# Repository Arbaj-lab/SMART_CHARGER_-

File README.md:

A compact, efficient, and automated smart charging trigger system built using an ATtiny 402 microcontroller, relays, and an IR sensor. This project automates the charging process with a custom-designed PCB.
Features
Automated Charging Trigger: Monitors charging conditions and activates relays as required.
IR Sensor Integration: Detects specific conditions to enable/disable the charging process.
Custom PCB Design: Compact and optimized for real-world applications.
Arduino-Based Programming: Simple, modular code for easy customization.

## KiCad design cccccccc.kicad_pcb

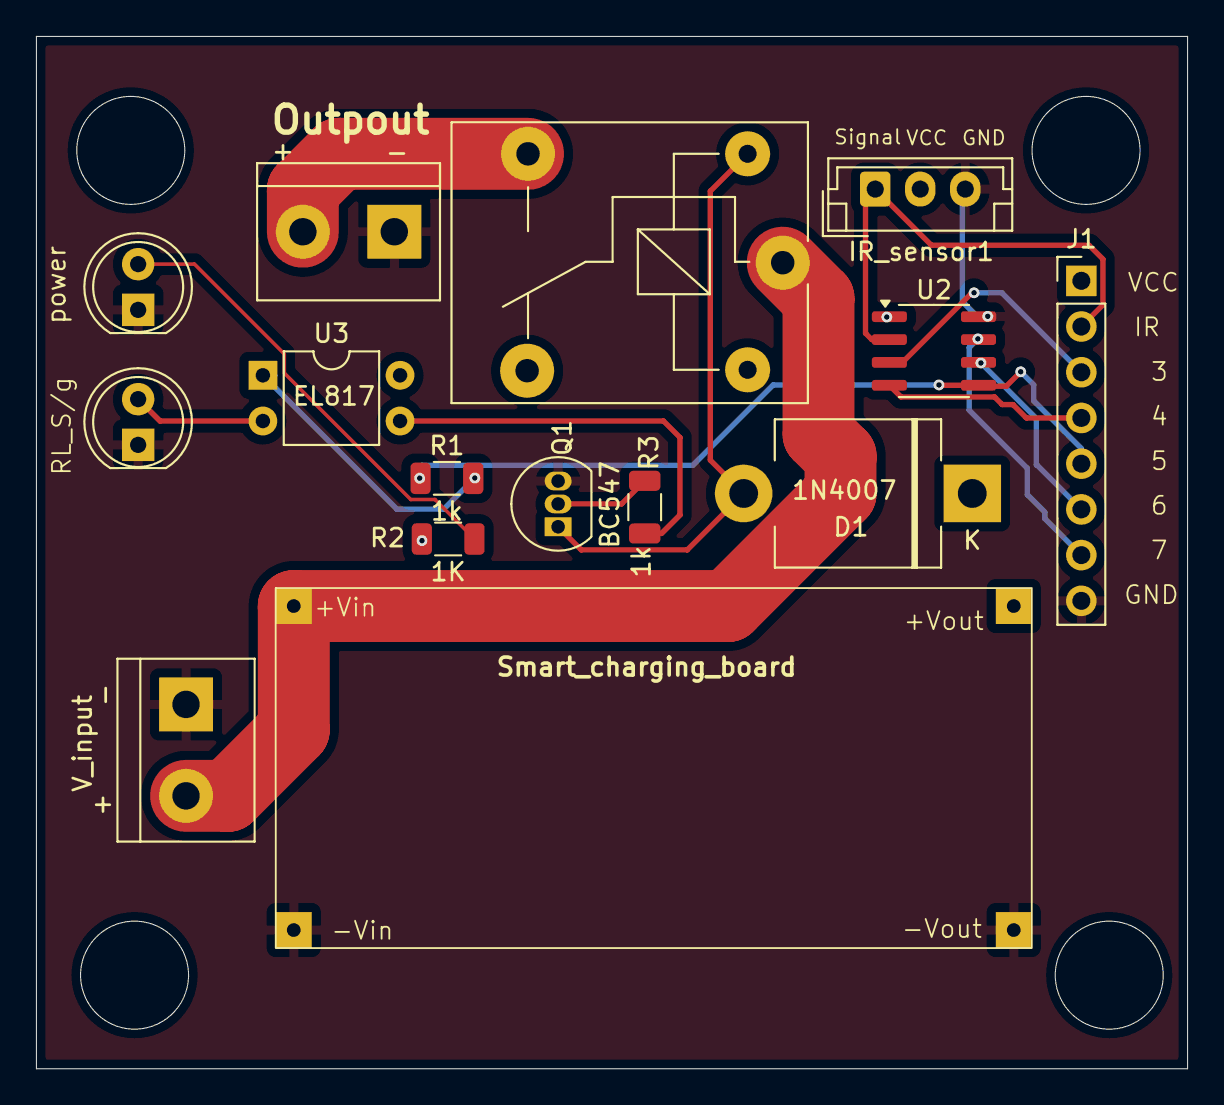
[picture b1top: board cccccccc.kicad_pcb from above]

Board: 2 copper layers, 63.9 x 57.4 mm, 15 parts (0 on the bottom side), 16 nets.

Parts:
D1: 1N4007; D_5KPW_P12.70mm_Horizontal
IR_sensor1: Conn_01x03_Socket; JST_EH_B3B-EH-A_1x03_P2.50mm_Vertical
J1: Conn_01x08_Pin; PinHeader_1x08_P2.54mm_Vertical
K1: SANYOU_SRD_Form_C; Relay_SPDT_SANYOU_SRD_Series_Form_C
Output_16v1: Screw_Terminal_01x02; TerminalBlock_bornier-2_P5.08mm
Q1: BC547; TO-92_Inline
R1, R3: 1k; R_1206_3216Metric
R2: 1K; R_1206_3216Metric
RL_S/g: LED; LED_D5.0mm
U1: Lm2596_AA
U2: ATtiny402-SS; SOIC-8_3.9x4.9mm_P1.27mm
U3: EL817; DIP-4_W7.62mm
V_input: Screw_Terminal_01x02; TerminalBlock_bornier-2_P5.08mm
power: LED; LED_D5.0mm

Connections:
/16V: K1.1, U1.1 (+Vin), V_input.2
/GND_S: IR_sensor1.3, J1.8, Output_16v1.1, Q1.3 (E), RL_S/g.1 (K), U1.2 (-Vin), U1.4 (-Vout), U2.8 (GND), V_input.1, power.1 (K)
/Relay_Signal_5: J1.5, R1.1, U2.5 (PA2)
/VCC: D1.1 (K), IR_sensor1.2, J1.1, K1.5, R2.1, U1.3 (+Vout), U2.1 (VCC), U3.4
/pin3: J1.3, U2.3 (PA7)
/pin_2_IR: IR_sensor1.1, J1.2, U2.2 (PA6)
/pin_4: J1.4, U2.4 (PA1)
/pin_6: J1.6, U2.6 (~RESET/PA0)
/pin_7: J1.7, U2.7 (PA3)
unnamed: D1.2 (A), K1.2, Q1.1 (C)
unnamed: RL_S/g.2 (A), U3.2
unnamed: K1.3, Output_16v1.2
unnamed: Q1.2 (B), R3.2
unnamed: R1.2, U3.1
unnamed: R3.1, U3.3
unnamed: R2.2, power.2 (A)
